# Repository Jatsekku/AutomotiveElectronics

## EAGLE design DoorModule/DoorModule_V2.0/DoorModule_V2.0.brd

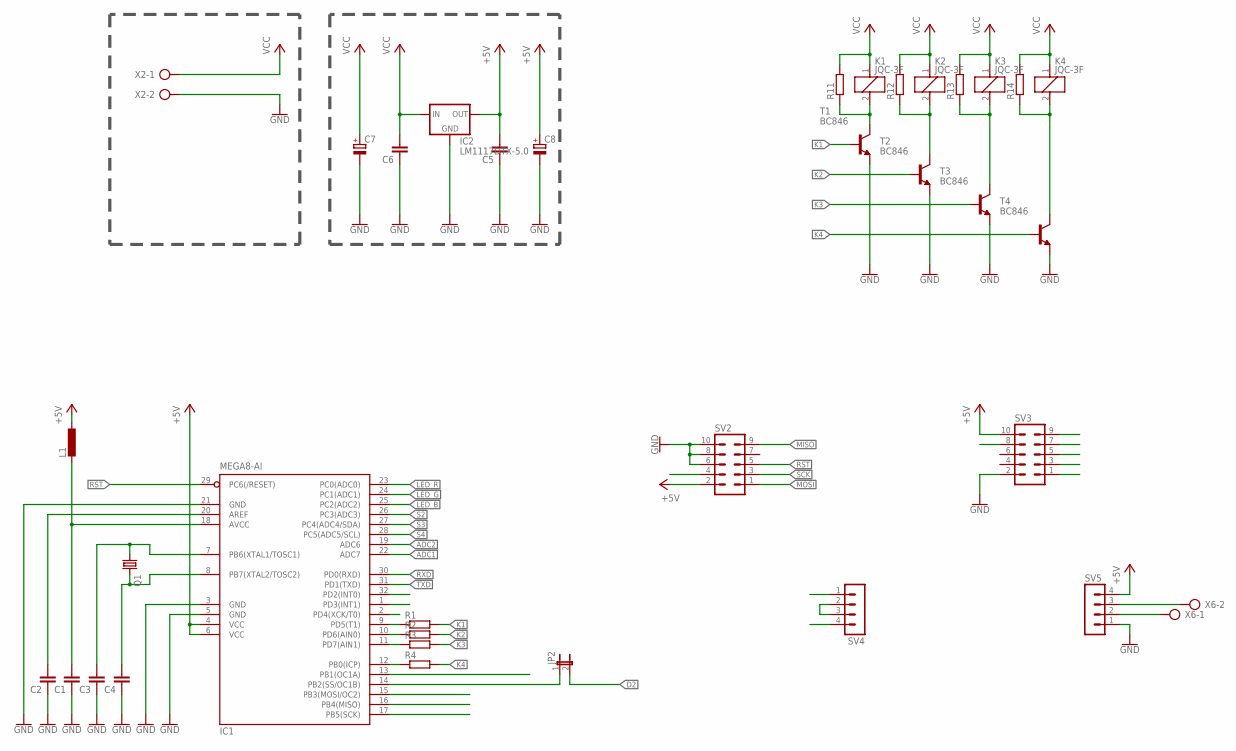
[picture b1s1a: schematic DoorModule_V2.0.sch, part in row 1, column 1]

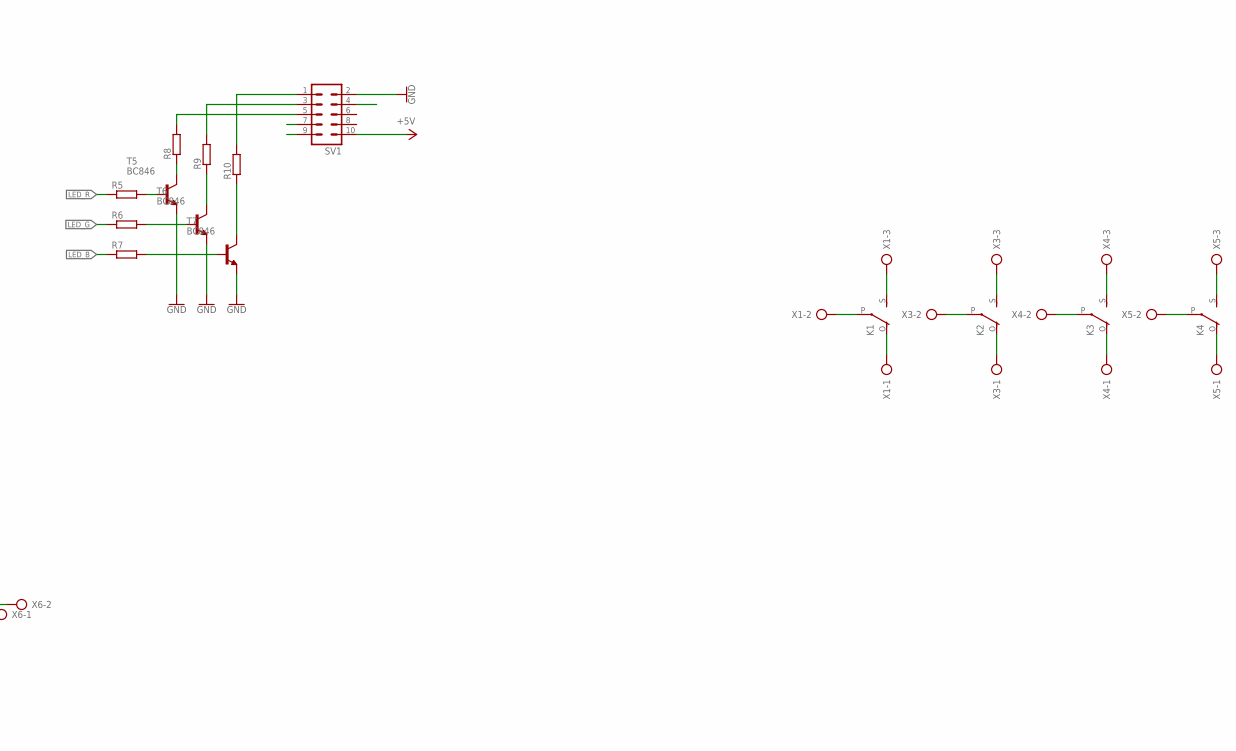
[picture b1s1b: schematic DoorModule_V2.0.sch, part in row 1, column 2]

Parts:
C1, C2, C3, C4, C5, C6: C-EUC0805; C0805
C7, C8: CPOL-EUE2.5-7; E2,5-7
IC1: MEGA8-AI; TQFP32-08
IC2: LM1117DTX-5.0; TO252
JP2: JP1E; JP1
K1, K2, K3, K4: JQC-3F; G5LE
L1: L-EU0204/7; 0204/7
Q1: CRYSTALHC49U-V; HC49U-V
R1, R2, R3, R4, R5, R6, R7, R10, R11, R12, R13, R14: R-EU_R0805; R0805
R8, R9: R-EU_0204/7; 0204/7
SV1, SV2, SV3: ML10L
SV4, SV5: MA04-1
T1, T2, T3, T4, T5, T6, T7: BC846; SOT23
X1, X3, X4, X5: AK300/3
X2, X6: AK300/2

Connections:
+5V: C5.2, C8.+, IC1.4 (VCC), IC1.6 (VCC), IC2.TAB (OUT), L1.1, SV1.10, SV2.2, SV3.10, SV5.4
ADC1: IC1.22 (ADC7), SV3.1
ADC2: IC1.19 (ADC6), SV3.3
D1: IC1.13 (PB1(OC1A)), SV1.4
D2: JP2.2, SV2.4
GND: C1.1, C2.1, C3.1, C4.1, C5.1, C6.1, C7.-, C8.-, IC1.3 (GND), IC1.5 (GND), IC1.21 (GND), IC2.1 (GND), SV1.2, SV2.6, SV2.8, SV2.10, SV3.2, SV5.1, T1.2 (E), T2.2 (E), T3.2 (E), T4.2 (E), T5.2 (E), T6.2 (E), T7.2 (E), X2.2
INT0: IC1.32 (PD2(INT0)), SV3.9
INT1: IC1.1 (PD3(INT1)), SV3.8
K1: R1.2, T1.1 (B)
K2: R2.2, T2.1 (B)
K3: R3.2, T3.1 (B)
K4: R4.2, T4.1 (B)
LED_B: IC1.25 (PC2(ADC2)), R7.1
LED_G: IC1.24 (PC1(ADC1)), R6.1
LED_R: IC1.23 (PC0(ADC0)), R5.1
MISO: IC1.16 (PB4(MISO)), SV2.9
MOSI: IC1.15 (PB3(MOSI/OC2)), SV2.1
unnamed: K1.S, X1.3
unnamed: K1.O, X1.1
unnamed: K1.P, X1.2
unnamed: K2.S, X3.3
unnamed: C1.2, IC1.18 (AVCC), L1.2
unnamed: C2.2, IC1.20 (AREF)
unnamed: C3.2, IC1.7 (PB6(XTAL1/TOSC1)), Q1.1
unnamed: C4.2, IC1.8 (PB7(XTAL2/TOSC2)), Q1.2
unnamed: R8.2, SV1.5
unnamed: K1.2, R11.1, T1.3 (C)
unnamed: K2.2, R12.1, T2.3 (C)
unnamed: R5.2, T5.1 (B)
unnamed: R6.2, T6.1 (B)
unnamed: R7.2, T7.1 (B)
unnamed: R8.1, T5.3 (C)
unnamed: R9.1, T6.3 (C)
unnamed: R10.1, T7.3 (C)
unnamed: R9.2, SV1.3
unnamed: R10.2, SV1.1
unnamed: K3.2, R13.1, T3.3 (C)
unnamed: K4.2, R14.1, T4.3 (C)
unnamed: IC1.9 (PD5(T1)), R1.1
unnamed: IC1.10 (PD6(AIN0)), R2.1
unnamed: IC1.11 (PD7(AIN1)), R3.1
unnamed: IC1.12 (PB0(ICP)), R4.1
unnamed: K2.P, X3.2
unnamed: K2.O, X3.1
unnamed: K3.P, X4.2
unnamed: K3.S, X4.3
unnamed: K3.O, X4.1
unnamed: K4.S, X5.3
unnamed: K4.P, X5.2
unnamed: K4.O, X5.1
unnamed: SV5.3, X6.2
unnamed: SV5.2, X6.1
RS: IC1.2 (PD4(XCK/T0)), SV4.2, SV4.3
RST: IC1.29 (PC6(/RESET)), SV2.5
RXD: IC1.30 (PD0(RXD)), SV4.1
S2: IC1.26 (PC3(ADC3)), SV1.7
S3: IC1.27 (PC4(ADC4/SDA)), SV3.5
S4: IC1.28 (PC5(ADC5/SCL)), SV3.7
SCK: IC1.17 (PB5(SCK)), SV2.3
SS: IC1.14 (PB2(SS/OC1B)), JP2.1
TXD: IC1.31 (PD1(TXD)), SV4.4
VCC: C6.2, C7.+, IC2.2 (IN), K1.1, K2.1, K3.1, K4.1, R11.2, R12.2, R13.2, R14.2, X2.1

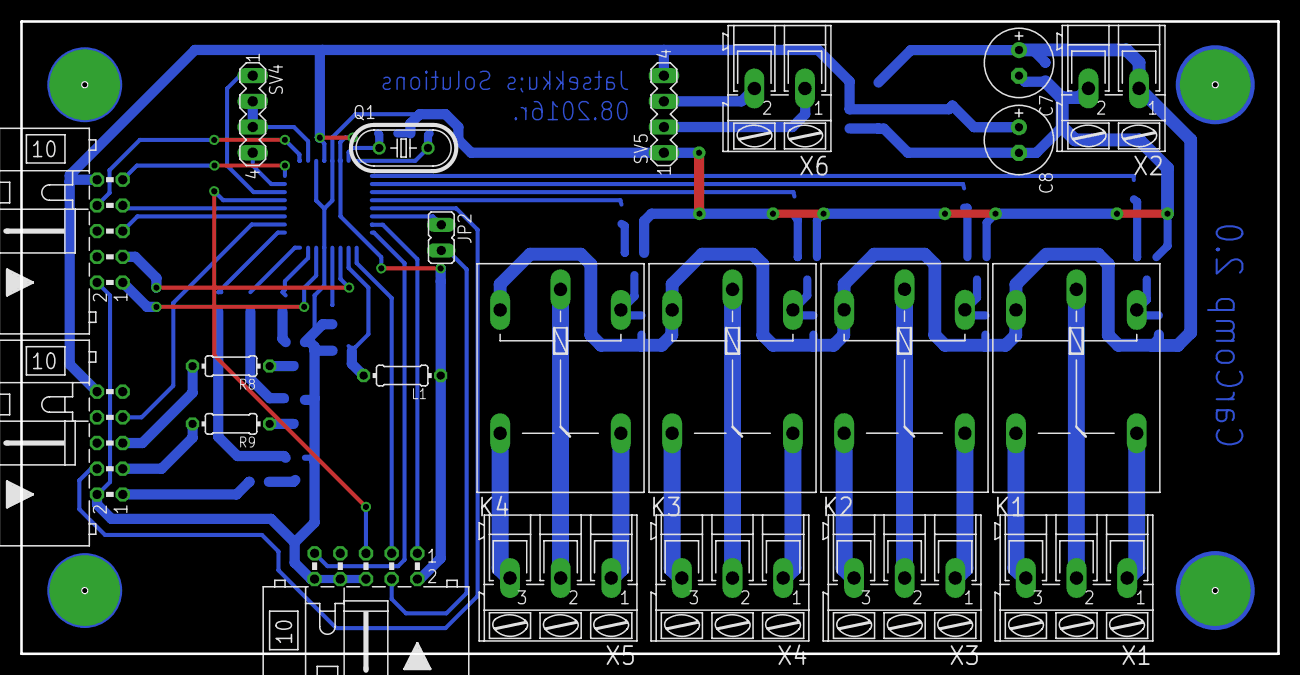
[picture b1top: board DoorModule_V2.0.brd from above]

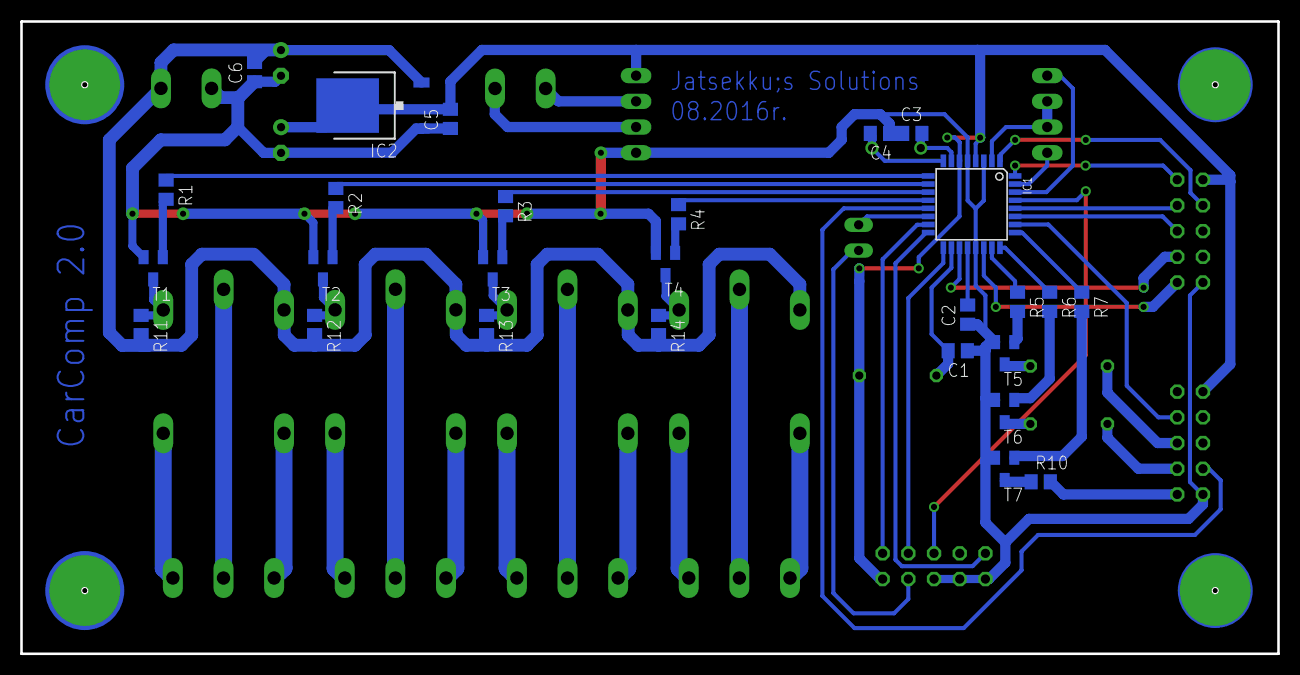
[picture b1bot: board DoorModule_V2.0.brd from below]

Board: 2 copper layers, 124.2 x 62.5 mm, 49 parts (27 on the bottom side), 62 nets.

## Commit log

2020-02-26 DoorModule Version 1.0
    Module contains:
    - 4 NO/NC relay-based outputs
    - 3 transistor-based outputs (BC846)
    - ATmega8 microcontroller
    - build-in voltage regulator
    The module was designed to provide control of central locking system and motors of electric windows.
2020-02-26 DoorModule Version 2.0
    Second version was redesigned to fit in universal enclosure available on the market.
    Moreover, new layout provides footprint for RS485 <-> UART converter as a new feature.
